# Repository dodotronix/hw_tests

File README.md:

# Hardware Tests

## List of projects
* Hotswap testbench (TPS2493PW)
* Breadboard SMD switch

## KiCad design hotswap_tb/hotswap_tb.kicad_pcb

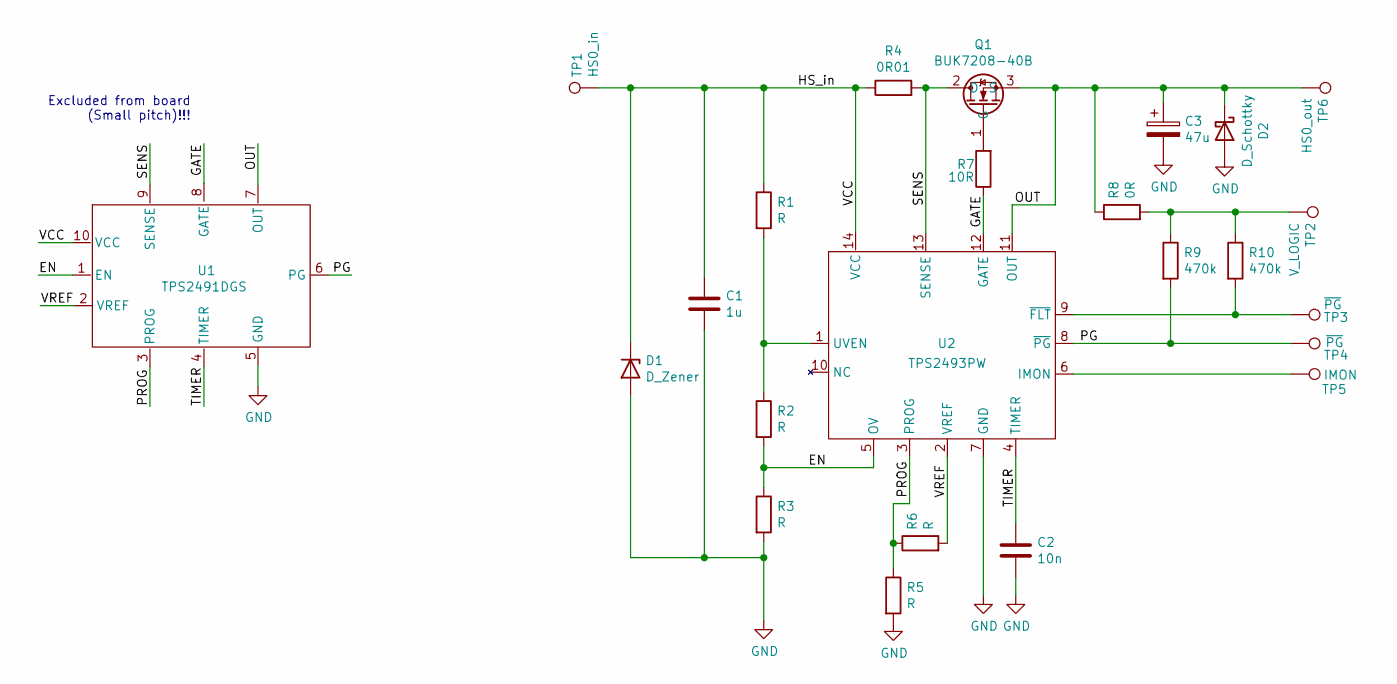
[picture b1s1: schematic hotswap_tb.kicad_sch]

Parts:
C1: 1u; C_0805_2012Metric_Pad1.18x1.45mm_HandSolder
C2: 10n; C_0805_2012Metric_Pad1.18x1.45mm_HandSolder
C3: 47u; CP_Elec_6.3x5.3
D1: D_Zener; D_0805_2012Metric_Pad1.15x1.40mm_HandSolder
D2: D_Schottky; D_0805_2012Metric_Pad1.15x1.40mm_HandSolder
Q1: BUK7208-40B; TO-252-2
R1, R2, R3, R5, R6: R; R_0805_2012Metric_Pad1.20x1.40mm_HandSolder
R4: 0R01; R_0805_2012Metric_Pad1.20x1.40mm_HandSolder
R7: 10R; R_0805_2012Metric_Pad1.20x1.40mm_HandSolder
R8: 0R; R_0805_2012Metric_Pad1.20x1.40mm_HandSolder
R9, R10: 470k; R_0805_2012Metric_Pad1.20x1.40mm_HandSolder
TP1: HS0_in; TestPoint_Pad_D2.5mm
TP2: V_LOGIC; TestPoint_Pad_D2.5mm
TP3, TP4: ~PG; TestPoint_Pad_D2.5mm
TP5: IMON; TestPoint_Pad_D2.5mm
TP6: HS0_out; TestPoint_Pad_D2.5mm
U1: TPS2491DGS; VSSOP-10_3x3mm_P0.5mm
U2: TPS2493PW; TSSOP-14_4.4x5mm_P0.65mm

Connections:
/EN: R2.2, R3.1, U1.1 (EN), U2.5 (OV)
/GATE: R7.1, U1.8 (GATE), U2.12 (GATE)
/HS_in: C1.1, D1.1 (K), R1.1, R4.1, TP1.1, U1.10 (VCC), U2.14 (VCC)
/OUT: C3.1, D2.1 (K), Q1.3 (S), R8.1, TP6.1, U1.7 (OUT), U2.11 (OUT)
/PG: R9.2, TP4.1, U1.6 (PG), U2.8 (~PG)
/PROG: R5.1, R6.1, U1.3 (PROG), U2.3 (PROG)
/SENS: Q1.2 (D), R4.2, U1.9 (SENSE), U2.13 (SENSE)
/TIMER: C2.1, U1.4 (TIMER), U2.4 (TIMER)
/VREF: R6.2, U1.2 (VREF), U2.2 (VREF)
GND: C1.2, C2.2, C3.2, D1.2 (A), D2.2 (A), R3.2, R5.2, U1.5 (GND), U2.7 (GND)
unnamed: Q1.1 (G), R7.2
unnamed: R1.2, R2.1, U2.1 (UVEN)
unnamed: R8.2, R9.1, R10.1, TP2.1
unnamed: R10.2, TP3.1, U2.9 (~FLT)
unnamed: TP5.1, U2.6 (IMON)

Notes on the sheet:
Excluded from board (Small pitch)!!!

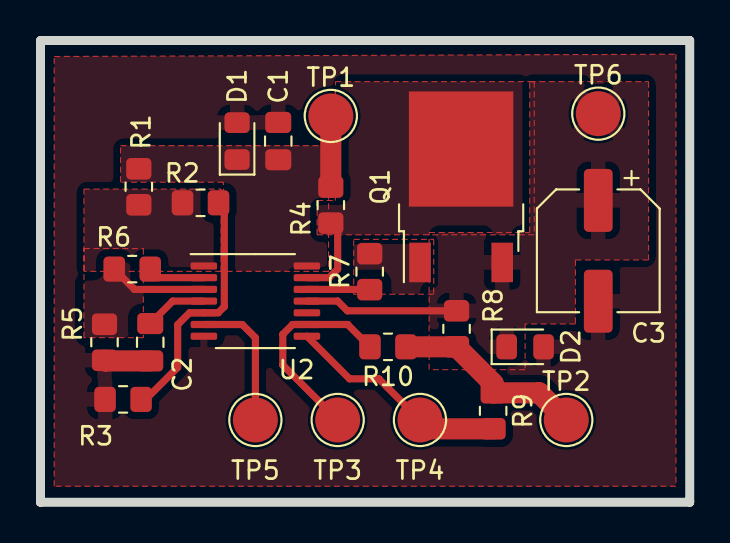
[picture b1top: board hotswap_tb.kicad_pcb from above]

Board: 2 copper layers, 36.1 x 25.7 mm, 23 parts (0 on the bottom side), 15 nets.

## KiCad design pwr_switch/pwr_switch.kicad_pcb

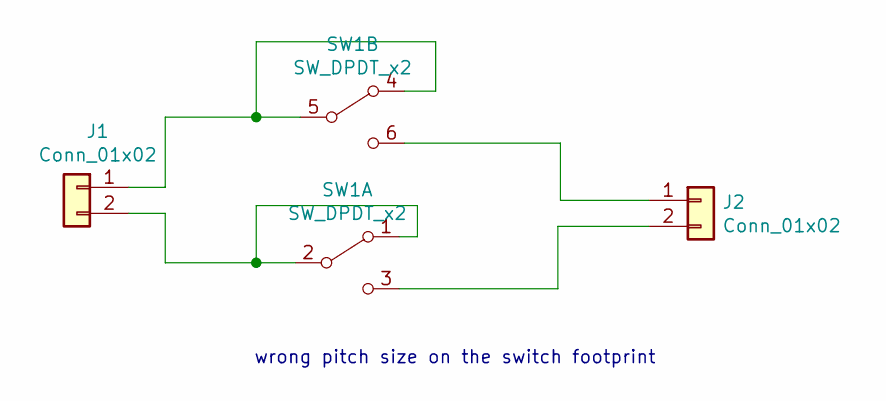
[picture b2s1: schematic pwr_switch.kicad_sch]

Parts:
J1, J2: Conn_01x02; PinHeader_1x02_P2.54mm_Vertical_SMD_Pin1Right
SW1: SW_DPDT_x2; dual_sw

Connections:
unnamed: J1.1, SW1.4 (A), SW1.5 (B)
unnamed: J1.2, SW1.1 (A), SW1.2 (B)
unnamed: J2.1, SW1.6 (C)
unnamed: J2.2, SW1.3 (C)

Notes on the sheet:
wrong pitch size on the switch footprint

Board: 2 copper layers, 3 parts (2 on the bottom side), 4 nets, no tracks yet.

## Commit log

2022-05-29 new readme
2022-05-29 new gitignore
2022-05-29 breadboard switch project
2022-05-29 manufacturing data for breadbord switch
2022-05-29 hotswap testbench
2022-05-29 manufacturing data for hotswap pcb
